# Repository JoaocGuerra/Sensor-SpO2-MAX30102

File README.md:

**Instituto Federal da Paraíba - Campus Campina Grande** \
**Curso:** Engenharia de Computação \
**Componente:** Técnicas de Prototipagem\ Alexandre Sales Vasconcelos
**Projeto**, Sensor-SpO2-MAX30102 

**Discentes:** \
João Carlos Guerra de Abreu \
João Gabriel de Oliveira Ponciano \
João Messias da Silva Medeiros 

**Descrição:** \
Fazer uso do sensor SpO2-MAX30102 para medir o batimento cardíaco e o nível de oxigênio no sangue, tratar os valores usando o ATmega328P, exibir os valores tratados no display Adafruit OLED 128×64×1 e o sistema vai ser alimentado por uma bateria moeda cujo o modelo é o cr2032 de 3volts. Todas essas ferramentas serão organizadas em uma case com pulseira de encaixe para virar uma pulseira de uso humano.

**As Dimensões da case da pulseira:**\
Comprimento: 7.59 cm\
Altura: 1.0 cm\
Largura: 3.9 cm

**Sobre a pulseira:**
Deverar se produzida tendo como exemplo a pulseira da Miband com um detalhe que seria os braços da pulseria no comprimento da pulseira e não na largura. Onde as dimensões são:\
Comprimento: 7.7 cm\
Altura: 1.2 cm\
Largura: 4.1 cm\
Onde a case ficará localizada dentro dela.\
Exemplo da pulseira:\

**Link para vídeos da entrega parcial:**\
Vídeo no Fusion: https://drive.google.com/file/d/1T5mHVWk34nRYTMkD_aoFN_-S5dbFVQ9f/view?usp=sharing \
Vídeo no PrusaSlicer: https://drive.google.com/file/d/1SkHnBMplbUZp8OetU9DAU1jy5QvF_HWb/view?usp=sharing 

**Link para vídeos da entrega final:**\
Vídeo no Fusion: https://drive.google.com/file/d/1dPndxY80PS835-GUdL-PTFbMv8hM3xNm/view?usp=sharing \
Vídeo no PrusaSlicer: https://drive.google.com/file/d/1EfMC83h38OxdnKpaQ8Ry-B_SHpYDWS-7/view?usp=sharing \

**Trabalhos futuros:**\
Como melhoria para o projeto, foi sugerido a alteração do display e do e a troca do Atmega por um componente CMS, assim o dispositivo ficaria mais compacto e teria um pouco mais de conforto para o usuário.

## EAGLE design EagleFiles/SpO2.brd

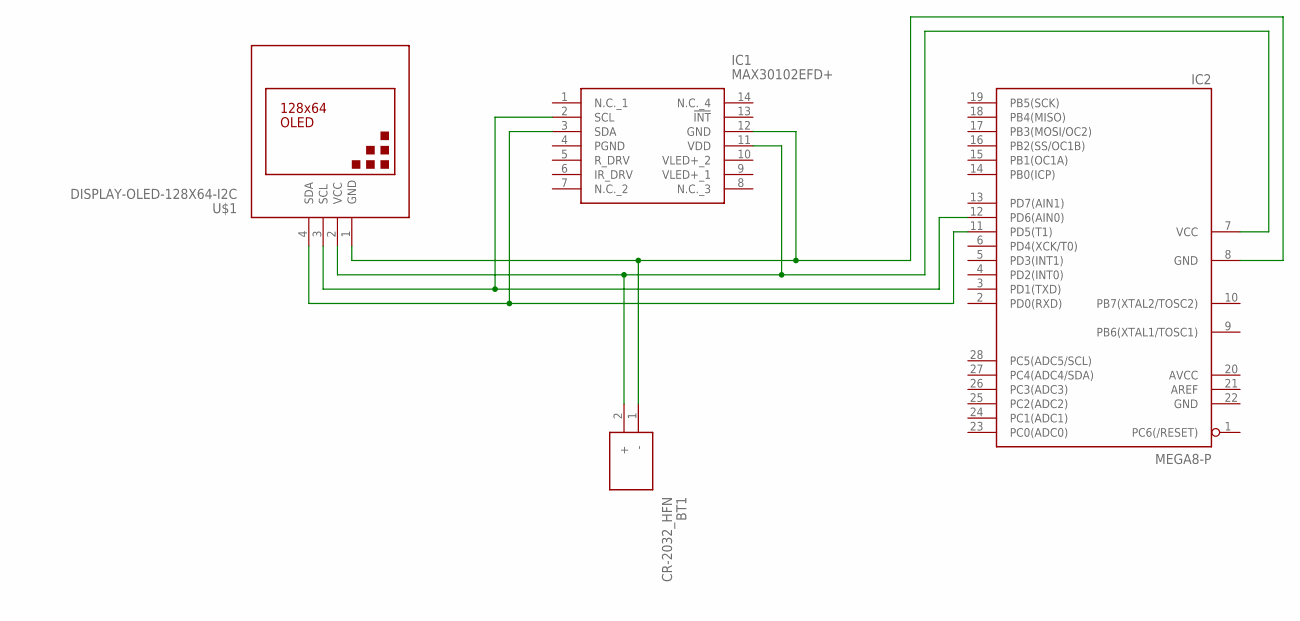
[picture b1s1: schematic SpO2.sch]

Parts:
BT1: CR-2032_HFN; CR-2032HFN
IC1: MAX30102EFD+; 14-LEAD-OESIP
IC2: MEGA8-P; DIL28-3
U$1: DISPLAY-OLED-128X64-I2C

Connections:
AVCC: IC2.20 (AVCC)
GND: IC2.22 (GND)
unnamed: IC1.2 (SCL), IC2.12 (PD6(AIN0)), U$1.3 (SCL)
unnamed: IC1.3 (SDA), IC2.11 (PD5(T1)), U$1.4 (SDA)
unnamed: BT1.2 (+), IC1.11 (VDD), IC2.7 (VCC), U$1.2 (VCC)
unnamed: BT1.1 (-), IC1.12 (GND), IC2.8 (GND), U$1.1 (GND)

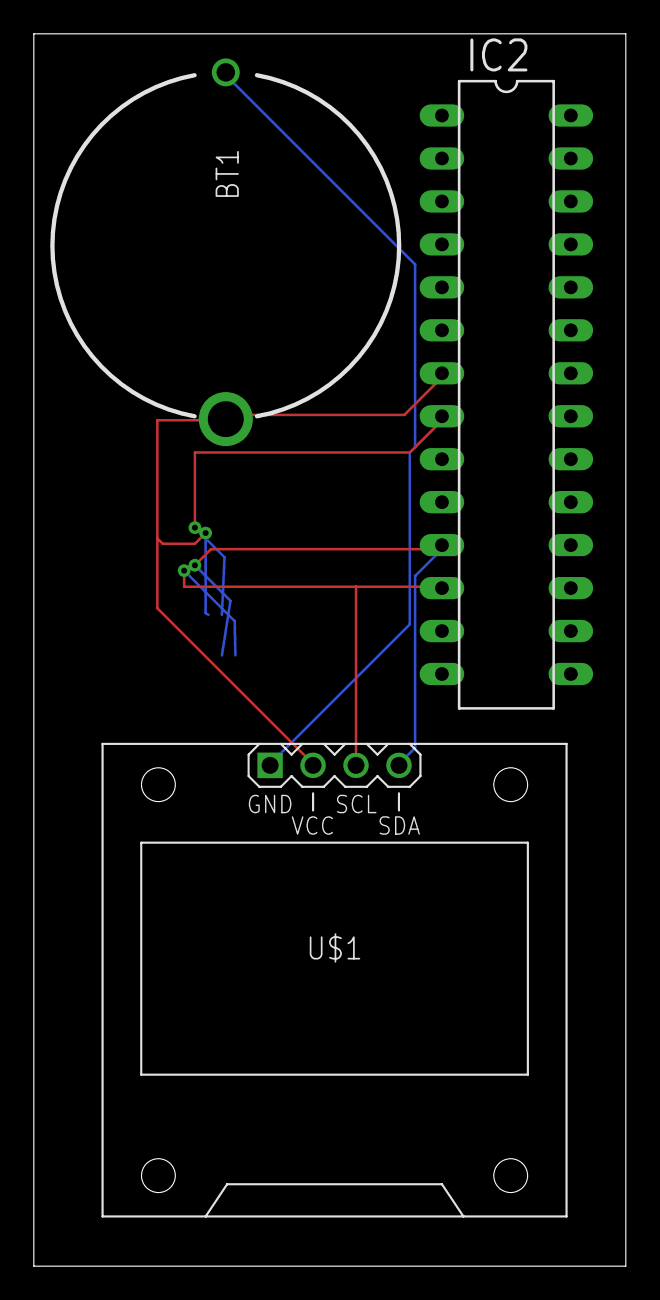
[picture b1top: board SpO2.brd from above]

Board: 2 copper layers, 35.0 x 72.9 mm, 4 parts (1 on the bottom side), 4 nets.

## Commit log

2021-10-13 FusionFiles
2021-10-13 PrusaSlicerFiles
2021-10-13 Dimesions atulizadas
2021-10-13 EagleFiles
2021-10-14 Adicionando ativiades do classroom
2021-10-14 Few changes added
2021-10-14 Projeto Final added

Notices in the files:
parts and their libraries:
diy-modules: Released under the Creative Commons Attribution 4.0 International License: http://creativecommons.org/licenses/by/4.0
